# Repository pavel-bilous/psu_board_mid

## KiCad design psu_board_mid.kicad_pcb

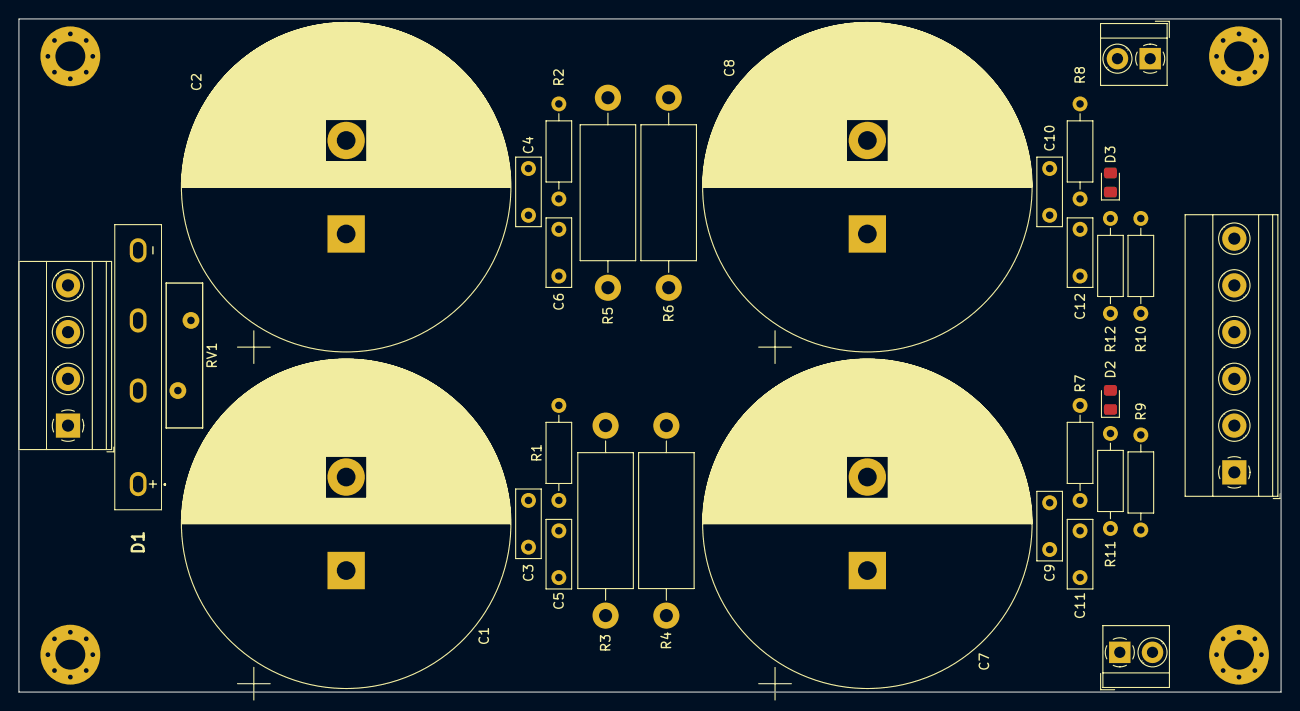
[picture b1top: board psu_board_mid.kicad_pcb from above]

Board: 2 copper layers, 135.0 x 72.0 mm, 36 parts (0 on the bottom side), 15 nets, no tracks yet.

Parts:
C1, C2, C7, C8: 22,000uF; CP_Radial_D35.0mm_P10.00mm_SnapIn
C3, C4, C5, C6, C9, C10, C11, C12: 100n; C_Rect_L7.2mm_W2.5mm_P5.00mm_FKS2_FKP2_MKS2_MKP2
D1: PB3510; PB3510E345
D2, D3: LED; D_0805_2012Metric_Pad1.15x1.40mm_HandSolder
H1, H2, H3, H4: MountingHole; MountingHole_3.2mm_M3_Pad_Via
J1: AC; TerminalBlock_Phoenix_MKDS-1,5-4_1x04_P5.00mm_Horizontal
J2, J3: LED; TerminalBlock_MetzConnect_Type059_RT06302HBWC_1x02_P3.50mm_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
J4: DC; TerminalBlock_Phoenix_MKDS-1,5-6_1x06_P5.00mm_Horizontal
R1, R2, R7, R8: 10R; R_Axial_DIN0207_L6.3mm_D2.5mm_P10.16mm_Horizontal
R3, R4, R5, R6: 0.47R 3W; R_Axial_DIN0614_L14.3mm_D5.7mm_P20.32mm_Horizontal
R9, R10, R11, R12: 10K; R_Axial_DIN0207_L6.3mm_D2.5mm_P10.16mm_Horizontal
RV1: MOV-14D101KTR; RV_Disc_D15.5mm_W3.9mm_P7.5mm

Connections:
/AC1: D1.2, J1.1, RV1.1
/AC4: D1.3, J1.4, RV1.2
/OV+: C7.1, C9.1, C11.1, J4.1, J4.2, R3.1, R4.1, R9.1, R11.1
/OV-: C8.2, C10.2, D3.2, J3.2, J4.5, J4.6, R5.1, R6.1, R8.2
/RV+: C1.1, C3.1, C5.1, D1.1, R3.2, R4.2
/RV-: C2.2, C4.2, D1.4, R2.2, R5.2, R6.2
GND: C1.2, C2.1, C3.2, C4.1, C6.1, C7.2, C8.1, C9.2, C10.1, C12.1, D2.2, J1.2, J1.3, J2.2, J4.3, J4.4, R1.2, R7.2, R10.1, R12.1
unnamed: C5.2, R1.1
unnamed: C6.2, R2.1
unnamed: C11.2, R7.1
unnamed: C12.2, R8.1
unnamed: D2.1, R11.2
unnamed: D3.1, R12.2
unnamed: J2.1, R9.2
unnamed: J3.1, R10.2
